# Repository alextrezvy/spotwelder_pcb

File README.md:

# spotwelder_pcb
A PCB for spotwelder drawn in KiCad.

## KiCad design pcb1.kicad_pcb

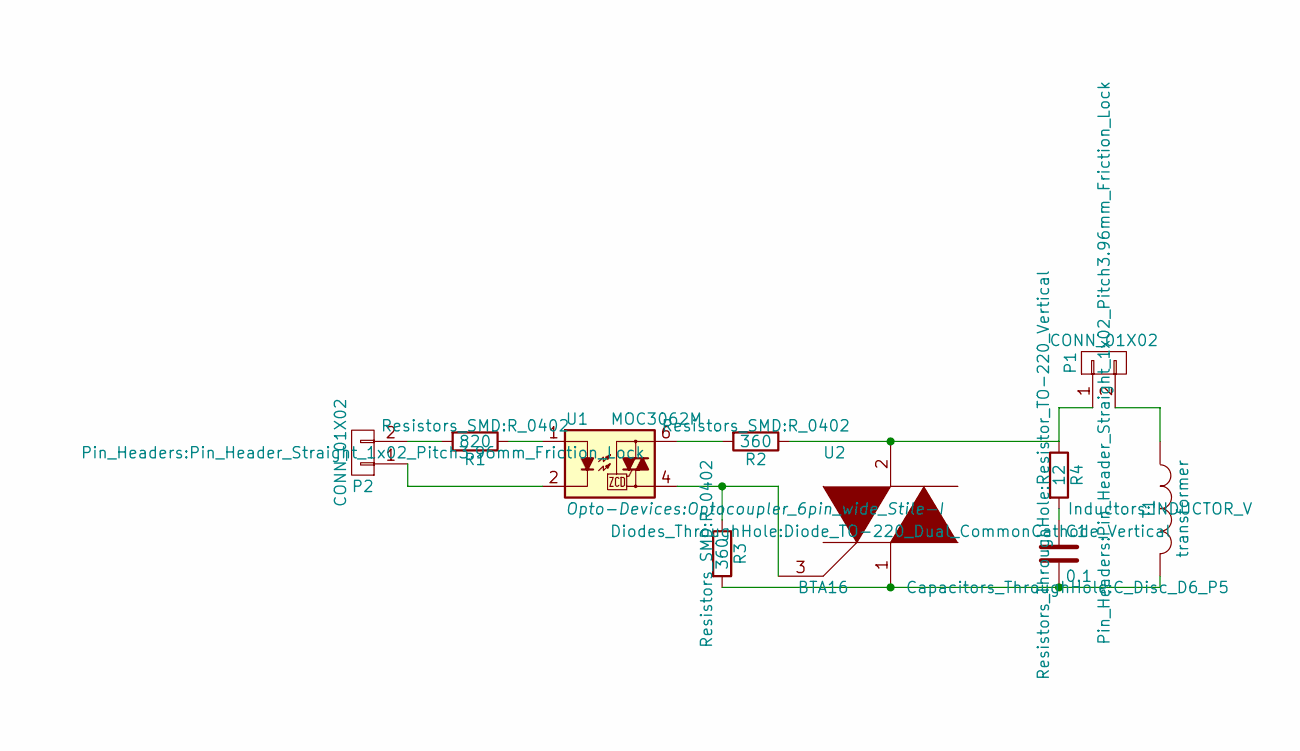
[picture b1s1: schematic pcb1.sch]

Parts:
C1: 0.1; C_Disc_D6_P5
P1, P2: CONN_01X02; Pin_Header_Straight_1x02_Pitch3.96mm_Friction_Lock
R1: 820; R_0402
R2, R3: 360; R_0402
R4: 12; Resistor_TO-220_Vertical
T1: transformer; INDUCTOR_V
U1: MOC3062M; Optocoupler_6pin_wide_Stile-I
U2: BTA16; Diode_TO-220_Dual_CommonCathode_Vertical

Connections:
unnamed: C1.1, R4.2
unnamed: C1.2, R3.2, T1.2, U2.1
unnamed: P1.1, R2.1, R4.1, U2.2
unnamed: P1.2, T1.1
unnamed: P2.1, U1.2
unnamed: P2.2, R1.2
unnamed: R1.1, U1.1
unnamed: R2.2, U1.6
unnamed: R3.1, U1.4, U2.3

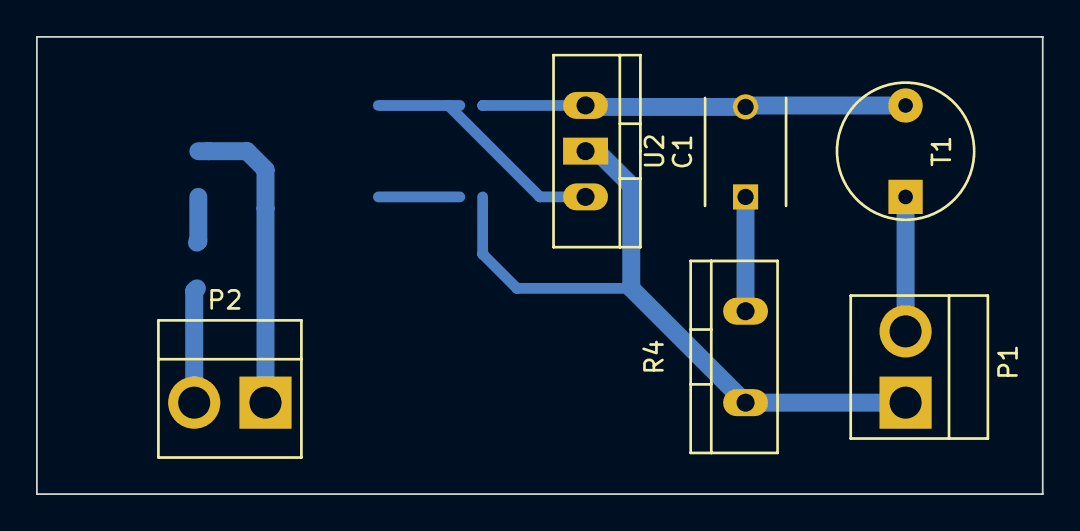
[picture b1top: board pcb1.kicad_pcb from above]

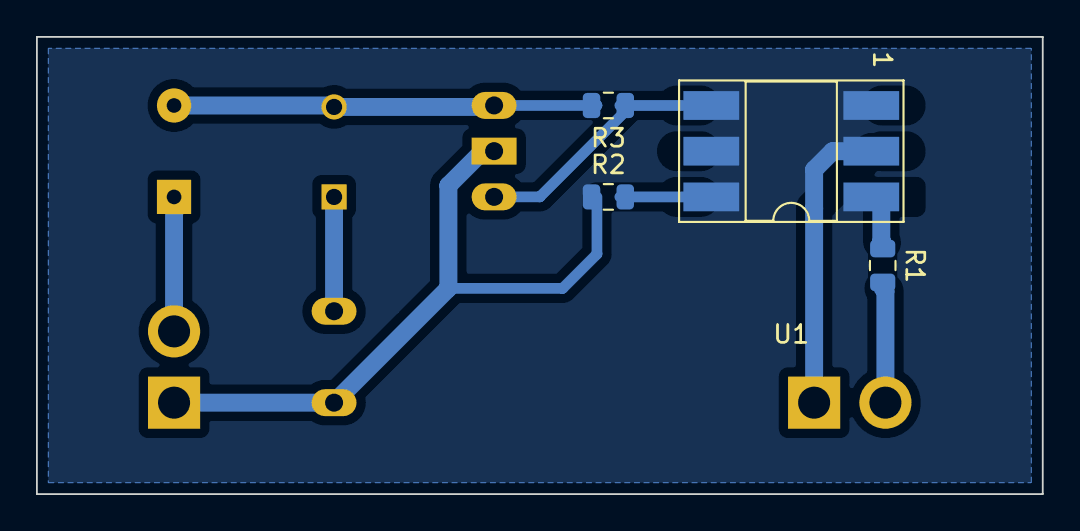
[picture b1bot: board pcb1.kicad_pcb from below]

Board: 2 copper layers, 55.9 x 25.4 mm, 10 parts (4 on the bottom side), 9 nets.

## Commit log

2020-03-23 PCB files initial commit
